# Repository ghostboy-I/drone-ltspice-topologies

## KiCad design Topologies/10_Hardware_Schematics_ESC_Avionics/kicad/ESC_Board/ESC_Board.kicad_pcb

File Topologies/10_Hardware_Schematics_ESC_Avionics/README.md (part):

# 10 — Hardware Schematics: ESC Board and Avionics Power Board

**Topology type:** topology 09 turned into two real PCBs with real parts. Each board is one LTspice schematic you can run, plus a BOM and a net list you can redraw in KiCad.

| Board | Qty per aircraft | What it does |
|---|---|---|
| **ESC board** (`ESC_Board.asc`) | 3 (one per motor) | 24S DC link → 3 × LTC7063 gate drivers → 24 × IPB065N15N3 (4 in parallel per switch) → U15XL. It has its own LTC7801 12 V aux supply, LT1763 5 V / 3.3 V, two ACS772 ±250 A current sensors and an STM32G431 running FOC. |
| **Avionics power board** (`Avionics_Board.asc`) | 1 | Three 24S packs → fuses + diode-OR → TVS + LTC4366 surge stopper (115 V) → LTC7801 12 V / 5 A (transmitter) → LT8641 5 V / 3 A (flight controller + receiver) → LT3045 3.3 V / 0.3 A (sensors). |

**Builds on:** [09](../09_24S_FOC_Drive_Low-Voltage_Rails/README.md) (the design these boards implement), [03](../03_Three-Phase_FOC_PMSM/README.md) (FOC), [06](../06_BEC_Synchronous_Buck_5V/README.md) (buck design), [08](../08_Redundant_Avionics_Power/README.md) (avionics fed from all three packs).
**Design document (with all the math):** `10_Hardware_Schematics_ESC_Avionics_Design.pdf`

## Files
| File | What it is |
|---|---|
| `board.py` | Builder: one parts table → `.asc` + BOM + net list (they can't drift apart) |
| `hand_calc.py` | All predictions (`python3 hand_calc.py`, `python3 hand_calc.py esc`) |
| `avionics.py`, `esc.py` | The two boards. `python3 avionics.py loop` also writes the loop-gain test |
| `*_BOM.csv` | Reference, quantity, description, value, part number / specification, **KiCad footprint**, rating |
| `*_Netlist.csv` | Every net with every `REF.pin` on it, the wiring list for KiCad (simulation-only parts removed) |
| `plot_results.py`, `make_design_doc.py` | Plots and the design PDF |
| `kicad_footprints.py`, `kicad_export.py`, `kicad_check.py` | KiCad: footprint library, both projects with PCBs, and the checks (see below) |
| `kicad_draw.py`, `kicad_avionics.py`, `kicad_esc.py`, `sexpr.py` | Both boards as drawn, hierarchical KiCad schematics (avionics five sheets, ESC eight), checked against the parts tables |
| `pcb_avionics.py`, `pcb_esc.py`, `kicad_route.py` | The two PCB layouts for JLCPCB: placement, pours, a grid router, DRC, Gerbers / BOM / CPL (see below) |

## Running the simulations
Open the `.asc` in LTspice and press Run, or in batch:
```bash
wine "$HOME/.wine/drive_c/Program Files/ADI/LTspice/LTspice.exe" -b ESC_Board.asc
```
| Run | Shows | Time |
|---|---|---|
| `Avionics_Board.asc` (8 ms) | Cold start and sequencing, transmitter switch-on, controller load step, pack 1 pulled | ~10 min |
| `Avionics_LoopTest.asc` | 12 V loop gain at 3 / 6 / 12 / 24 kHz by injection, on the switching circuit | ~5 min |
| `Avionics_SurgeTest.asc` (300 ms) | LTC4366 start-up, then pack 1 at 200 V behind 4 Ω for 20 ms: VIN_PROT must stay at 115 V | ~2 s |
| `ESC_Board.asc` (13 ms) | Cold start of the ESC electronics with the rotor at hover, flying start, throttle punch | ~7 min |

Parts named `V_…`, `B_…`, `L_HARN`, `R_CS…`, `R_BW…`, `C_BW…`, `La/Lb/Lc`, `C_J`, `C_TH`, `R_LK…`, `R_VBF`, `C_VBF`, `C_VTX`, `R_SSRUN`, `R_LOAD_SS` are simulation stimulus or models: the packs, the loads, the motor, and the STM32's FOC firmware as a behavioural block. Everything else is a board part with its real reference designator.

## Fixes from the parts-alternatives study
[Alternatives_Study](../Alternatives_Study/README.md) checked each section against datasheet ratings. Three problems are fixed here:
| Problem | Fix | Check |
|---|---|---|
| DC-link ripple 61.7 A rms at hover over 16 caps = 3.86 A each, above the 3.5 A rating | C65–C72: 8 more 150 µF 125 V hybrid polymer, 24 in all → 2.57 A each (3.48 A at punch, seconds only) | `python3 hand_calc.py changes`; ESC run `Icap_bulk`: 68.8 A → 2.87 A each at the run's iq of 160 A (hand 2.80) |
| Punch needs iq = 210 A; ACS770LCB-200B is specified to ±200 A | U7, U8 → ACS772ECB-250B: ±250 A, 8 mV/A, 200 kHz, same CB package and pinout. ADC still fits ±306 A, 151 mA/LSB | ESC run (firmware block uses 8 mV/A) |
| SMBJ110A clamps to 177 V at 3.4 A; the LTC7801 is rated to 150 V | U4 LTC4366-2 surge stopper + Q4 FDB33N25 (250 V): VIN_PROT held at VREG = 1.23 V (1 + R24/R23) = 115.3 V, 51 ms timer, 9 s cool-down | `Avionics_SurgeTest.asc`: 179 V in → 115.5 V out (hand 115.3 V) |

The LTC4366 takes ~0.1 s to turn Q4 on, so the 8 ms board run models Q4 already on (sim-only `R_SSRUN`, 94 mΩ), and its packs
ramp up from 0 V in 0.2 ms (the LTC4366 model has no DC operating point with the packs already at 88.8 V).

## Whole power system
The whole system, with both boards drawn part by part and wired to three packs and three motors, is now topology
[11](../11_Whole_System_Schematic/README.md) (`Power_System.asc`, the drawn board sheets and the KiCad entry guide).
The block diagram of everything, with part numbers, is in [System_Flowchart](../System_Flowchart/README.md).

## KiCad projects (both boards): schematic, footprints and PCB
```bash
python3 kicad_export.py all     # footprint library + both projects + overview plots
python3 kicad_check.py          # ERC, net list vs parts table, footprints, schematic-PCB parity (KiCad itself)
```
| Folder | What it is |
|---|---|
| `kicad/Drone_Power.pretty/` | **Every footprint both boards use (39).** 35 are KiCad 9 stock footprints, copied in under their KiCad names (`kicad_footprints.py`). 4 are not in KiCad's library and are generated from the manufacturers' drawings (table below) |
| `kicad/ESC_Board/` | The ESC board (197 parts): drawn schematic on eight sheets, and the **laid-out, routed PCB** (section below) |
| `kicad/Avionics_Board/` | The avionics board (77 parts): drawn schematic on five sheets, and the **laid-out, routed PCB** (next section) |
| `kicad/*_footprints.png` | KiCad's plot of each imported PCB: footprints parked by schematic block, ready for placement |

The PCBs are what **Tools → Update PCB from Schematic** would give: each footprint is linked to its symbol (same UUID path),
the nets come from KiCad's own net list of the schematic, and attributes (DNP, BOM) follow the symbols. The boards are laid
out by `pcb_avionics.py` and `pcb_esc.py`.

| Generated footprint | Part | Source |
|---|---|---|
| `Linear_UDC-18-2EP_3x4mm_P0.5mm` | LT8641 (avionics U2) | LT8641 datasheet Rev B: UDC 20(18)-lead QFN 3 × 4 mm, DWG 05-08-1956 Rev C. 0.25 × 0.70 mm lands at 0.5 mm, pins 5 and 12 removed, two exposed SW pads (21: 0.22 × 0.40 mm, 22: 0.22 × 0.356 mm) |
| `Linear_HTSSOP-24-1EP_4.4x7.8mm_P0.65mm_EP2.74x3.25mm` | LTC7801 (U1, both boards) | LTC DWG 05-08-1771 Rev B, FE24 exposed pad variation AA: 0.45 × 1.05 mm lands, exposed pad 2.74 × 3.25 mm = GND, 2 × 2 paste windows |
| `AMASS_AS150_Pigtail_2x8AWG_P15mm` | J1, ESC battery input | The AS150's two 8 AWG pigtail leads: 5.1 mm drill, 8.4 mm pads, 15 mm pitch (6.6 mm copper gap on the 100 V bus). Pad 1 = +, pad 2 = − |
| `SolderWire-8AWG_1x01_D4.2mm_OD7mm` | J2–J4, motor phase leads | 8 AWG silicone lead (4.2 mm conductor): KiCad's wire-pad rule, drill = conductor + 0.9 mm |

**Checked** (`kicad_check.py`): ERC 0 errors / 0 warnings on both boards; KiCad's net list equals the parts table on all
92 + 40 nets; every symbol pin has a pad of the same number; schematic-PCB parity 0 issues; polarised capacitors have pad 1
(+) off ground. Pads without a net are only unused MCU pins, the LTC7063 NC pins, TC2030 pad 6 (SWO) and connector
mounting tabs. Re-running the export gives identical files (UUIDs are derived from the board name).

**Corrected while importing the footprints**
- The LTC7801 had been given an HTSSOP-24 footprint whose 3.2 × 5 mm exposed pad comes from an ST drawing; ADI's FE24 pad is
  2.74 × 3.25 mm, so that land would have printed about 1.8× too much solder paste under the chip.
- The LT8641 is in ADI's UDC QFN (LT8641EUDC#PBF), not an LQFN: the BOM part number and package are fixed.
- J7 (Tag-Connect TC2030) had SWCLK and NRST swapped against the TC2030-CTX cable (pads 1 VCC, 2 SWDIO, 3 nRESET, 4 SWCLK,
  5 GND): now NRST is pad 3 and SWCLK pad 4.
- The motor phase pads were KiCad's 2.5 mm² wire pad, far too small for the 6–8 AWG phase leads; now 8 AWG pads.
- SMBJ110A is unidirectional, so it uses `Device:D_Zener` (K = 1, A = 2) instead of the bidirectional `D_TVS`; fuses use `Device:Fuse`.

## Avionics PCB layout (JLCPCB, 4 layers)
```bash
python3 pcb_avionics.py         # schematic -> placed, poured, routed, filled board + DRC + layout_routed.png (a few minutes)
python3 pcb_avionics.py place   # placement only, with layout_place.png
python3 pcb_avionics.py fab     # kicad/Avionics_Board/jlcpcb/: Gerber zip, BOM and CPL for JLC
```
The layout is a script, so a schematic change is one re-run. **Board:** 100 × 62 mm, 4 layers, 1.6 mm, 2 oz outer / 1 oz
inner (JLC04161H-7628 stackup), four M3 holes. In1 and In2 are solid ground planes; F.Cu carries the power pours; B.Cu has a
ground pour and the signal crossings. Power flows left to right: inputs → surge stopper → 12 V → 5 V → 3.3 V.

**Clearance rules** (`Avionics_Board.kicad_dru`, IPC-2221B table 6-1, B2 = external, uncoated). The spacing between two
conductors depends on the voltage *between* them, so nets are grouped by their peak voltage from the surge simulation:

| Group (net class) | Nets | Peak | Outer-layer clearance |
|---|---|---|---|
| HVIN | PACK1–3+, PACK1–3_F, VIN_AV | 200 V (pack surge) | 1.25 mm to LV and HVSW, 0.6 mm to HVF |
| HVF | VIN_PROT and the floating LTC4366 nets | ≤ 122 V | 0.6 mm |
| HVSW | SW12, BST12, TG12 | 0–126 V | 0.6 mm |
| LV (PWR, DRV, signal) | +12V, +5V, +3V3, GND, gate drive, control | ≤ 13 V | 0.2 mm |

Inner layers use 0.5 mm (B1 asks only 0.2 mm). Inside a group the spacing is 0.2 mm. The LTC7801's own pinout puts VIN 0.65 mm
from low-voltage pins, so its pin field (`U1_PINS` rule area, F.Cu) allows 0.2 mm. **Conformal-coat the board** (IPC B4).

**How it is checked**
- KiCad's DRC (`kicad-cli pcb drc` with schematic parity): `Avionics_Board_drc.json`, summary in `layout_stats.json`.
- `pinfield_audit()`: the U1 exemption must not reach copper outside the pin field. Every exempt item is cut back to the
  copper outside the area and the gaps that are left must meet the full rule.
- Before trusting a DRC of 0, make sure it loaded the rules. pcbnew's `LoadBoard` skips the `.kicad_dru`, so the zone filler
  needs the rules loaded first (`WriteDRCReport`). A reload in the same process also reuses a cached project, net classes and all.
  The script handles both (`fill()`, `load()`), and `load()` asserts that the HV classes are present.

**Results** (from `layout_stats.json`): 77 parts + 4 M3 holes; 512 tracks (F.Cu 498 mm, B.Cu 225 mm) and 114 vias; **0 unrouted, KiCad DRC 0 errors / 0 warnings with the HV rules loaded, schematic parity 0, pin-field audit 0.** Measured independently (KiCad's shape collision test), the ground pours sit ≥ 1.25 mm from HVIN copper and ≥ 0.6 mm from HVF / HVSW on the outer layers, and ≥ 0.5 mm on the inner planes. C10 and C23 have their references on F.Fab only (no silkscreen room).

`board_3d_top.png` is `kicad-cli pcb render --side top`. U1, U2 and the input connectors have no 3D model, so you see their pads.

**Ordering at JLCPCB** (`kicad/Avionics_Board/jlcpcb/`): upload `Avionics_Board_gerbers.zip`, choose 4 layers, 1.6 mm,
outer copper 2 oz, inner 1 oz, impedance control off (stackup JLC04161H-7628). For assembly, add `Avionics_Board_BOM_JLC.csv`
and `Avionics_Board_CPL_JLC.csv`. The LCSC column is empty, so pick each part in JLC's matcher, and **check every rotation
in JLC's 3D preview**: zero orientations differ between KiCad and JLC for SOT-23s, diodes and polarised parts.

Open items before ordering:
- F1–F3 are rated 125 V DC, but the surge test drives a pack input to 200 V. The fuse only has to survive it, not break
  it (the TVS and LTC4366 clamp downstream), but a 250 V DC-rated fuse in the same footprint removes the question.
- C26 is the 250 V 1206 part (it sits on the 100–121 V node).

## ESC PCB layout (JLCPCB, 4 layers + bus bars)
```bash
python3 pcb_esc.py              # schematic -> placed, poured, routed, filled board + DRC + renders + stats (~6 min)
python3 pcb_esc.py place        # placement only, with layout_place.png
python3 pcb_esc.py copper       # power copper and hand vias only, filled, with layout_copper.png and DRC
python3 pcb_esc.py check        # independent clearance measurement of the saved board, into layout_stats.json
python3 pcb_esc.py fab          # kicad/ESC_Board/jlcpcb/: Gerber zip, BOM and CPL for JLC
```
**Board:** 175 × 130 mm, 4 layers, 1.6 mm, 2 oz outer / 1 oz inner (JLC04161H-7628), four M3 holes. The floorplan follows
the current. At the top is the DC link: 24 polymer capacitors in three rows of eight, with the battery pigtail J1 to their
right. Below them sit the three legs side by side, each a column of four high-side D2PAKs, a phase lane, four low-side
D2PAKs and a ground lane. The next leg's DC-link ceramics sit across each ground lane. Along the bottom is the low-current
band (drivers, current sensors, motor-lead pads, MCU, LDOs, connectors), and the aux 12 V buck is in the top-right corner.
Battery current flows top to bottom and motor current leaves at the bottom, so no high current crosses the MCU, and one
solid ground plane (In1) serves power and signal ground.

**Power copper.** VBUS, the phases and ground are pours on all four layers, sized by counting squares (design doc sec. 9).
Mask-free strips take a soldered copper bar (4 × 2 mm, or flattened 8 AWG): the three phase lanes, the VBUS strip along
the tops of the legs and the bridge from J1. Every FET tab has 30 thermal vias. The B.Cu under each FET column is opened
for the heat sink, which needs an insulating pad, because that copper is at VBUS or phase potential.

**Clearance rules** (`ESC_Board.kicad_dru`). These are the avionics board's groups, extended to 24S (100.8 V):

| Group (net class) | Nets | Voltage | Outer clearance |
|---|---|---|---|
| HVBUS | VBUS | 0–100.8 V | 0.6 mm to every other class |
| SW_A / SW_B / SW_C | PH_x, BST_x, TG_x, HS gates, MOT_x | −1 to 113 V | 0.6 mm (0.2 mm inside one phase) |
| SW_AUX | aux SW, BST, TG | 0–113 V | 0.6 mm |
| HVDIV1 / HVDIV2 | bus divider taps | 67 V / 34 V | 0.6 mm |
| LV (PWR, DRV, signal) | GND, +12V, +5V, +3V3, LS gates, control | ≤ 13 V | 0.2 mm |

Each phase is its own group: two phases can be the full bus apart, while a phase, its bootstrap supply and its high-side
gates move together. Inner layers use 0.3 mm (B1 asks only 0.2 mm). The LTC7063s and the LTC7801 put 100 V pins 0.2–0.25 mm from
low-voltage ones, so their pin fields are exempt rule areas (0.2 mm), checked by `pinfield_audit()`. **Conformal-coat the board.**

**Routing.** This uses the same A* router (`kicad_route.py`), with the hard spots planned by hand:
- **The LTC7801's left pin row escapes through a two-column via fan-out** (alternate pins 1.22 / 2.27 mm out). VBUS sits
  between NDRV and EXTVCC there, so no single-layer order works (What went wrong, 13).
- **FAULT_N drops to B.Cu through a via under each driver's pin 3.** It and DRV_EN are buses on neighbouring pins of all
  three drivers, so whichever routes first walls in the other.
- **R5's +3V3 routes before the encoder bus**, which would otherwise wall it in.
- **`tidy()` necks a track down to the pad's narrow side less 0.05 mm where it ends in a pad.** The router snaps the
  last point onto the exact pad centre, up to 25 µm off the grid it checked. `tidy()` also removes vias that two
  fan-outs put on the same spot.
- **Fan-out vias keep the full grid error** (cell × √2). KiCad's DRC caught one placed with only 0.75 cell, 0.196 mm from
  an LQFP pin.

**How it is checked**
- KiCad's DRC with schematic parity, with the HV rules loaded: `ESC_Board_drc.json`.
- `pinfield_audit()`: the exemptions must not reach copper outside the pin fields.
- `measure_gaps()` is an independent measurement that doesn't use KiCad's DRC engine. Per layer, all copper of each group
  (pads, tracks, vias, zone fills) becomes one polygon set. One set is grown by d (Clipper) and intersected with the
  other, bisecting d to 1 µm.

**Results** (`layout_stats.json`): 197 parts + 4 M3 holes; 1061 tracks (F.Cu 1598 mm, B.Cu
1161 mm) and 2147 vias (1974 placed by hand: 720 in FET tabs, 468 at the FET sources,
429 in the ground lanes, 288 in the capacitor bank). **0 unrouted, KiCad DRC 0 errors / 0 warnings, schematic parity 0,
pin-field audit 0.** Measured independently, every HV group keeps at least 0.600 mm from the other groups on F.Cu and B.Cu
and 0.300 mm on In1/In2. The closest pairs sit exactly at the rule, where the zone filler puts a pour.
6 references (Q8, Q25, Q17, R12, R15, R14) are on F.Fab only, because there was no room on the silkscreen.

**Ordering at JLCPCB** (`kicad/ESC_Board/jlcpcb/`): upload `ESC_Board_gerbers.zip` and choose:
- 4 layers, 1.6 mm, outer copper 2 oz, inner 1 oz.
- **Via covering "epoxy filled & capped"**: the thermal vias sit in the D2PAK tab pads, so open vias would wick the solder away.

For assembly, add `ESC_Board_BOM_JLC.csv` and `ESC_Board_CPL_JLC.csv`. The LCSC column is empty, so pick each part in JLC's
matcher, and check every rotation in JLC's 3D preview (D2PAKs, diodes, polarised capacitors, SOT-223).

Fit by hand after assembly:
1. Solder the copper bars on the mask-free strips.
2. Fit J1 (AS150 pigtails) and the 8 AWG motor leads.
3. Fit the heat sink over a ≥ 0.5 mm, ≥ 3 W/m·K, 150 V-rated insulating pad.
4. Conformal-coat the board.

R6 (the NTC) sits at the bottom of leg B's ground lane, on the board copper next to the FETs, not on the sink.

## Porting to KiCad by hand
1. **One schematic per board**, with one hierarchical sheet per numbered block (the framed areas in the `.asc`): e.g. ESC = 1 power input, 2 aux supply, 3 logic supplies, 4–6 legs A/B/C, 7 current sense, 8 MCU and connectors. Use global labels for the nets that cross sheets (`VBUS`, `+12V`, `+5V`, `+3V3`, `PWM_A`…).
2. **Symbols.** KiCad's stock library has the STM32G431CBTx, the ACS770/ACS772 CB-package symbol, the LT3045 and the AS5047. The **LTC7801, LTC7063, LT8641, LT1763 and LTC4366 are not in KiCad's library**: use the generated ones in `kicad/<Board>/<Board>_custom.kicad_sym`. Pin names in the net list are LTspice's names (`SENSE+`, `BGRTN`, `_FLT` = FLT-bar, `_SHDN` = SHDN-bar); match them to the datasheet pin names, not to pin numbers.
3. **Wire from `*_Netlist.csv`**: each row is one net and every pin on it. Parts listed with a quantity (e.g. `Q4 Q5 Q6 Q7`) are parallel copies with identical connections.
4. **Footprints** are all in `kicad/Drone_Power.pretty` (add it to your footprint library table). The BOM gives each one by its KiCad library name; the four `Drone_Power:` ones are generated from the manufacturers' drawings.
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
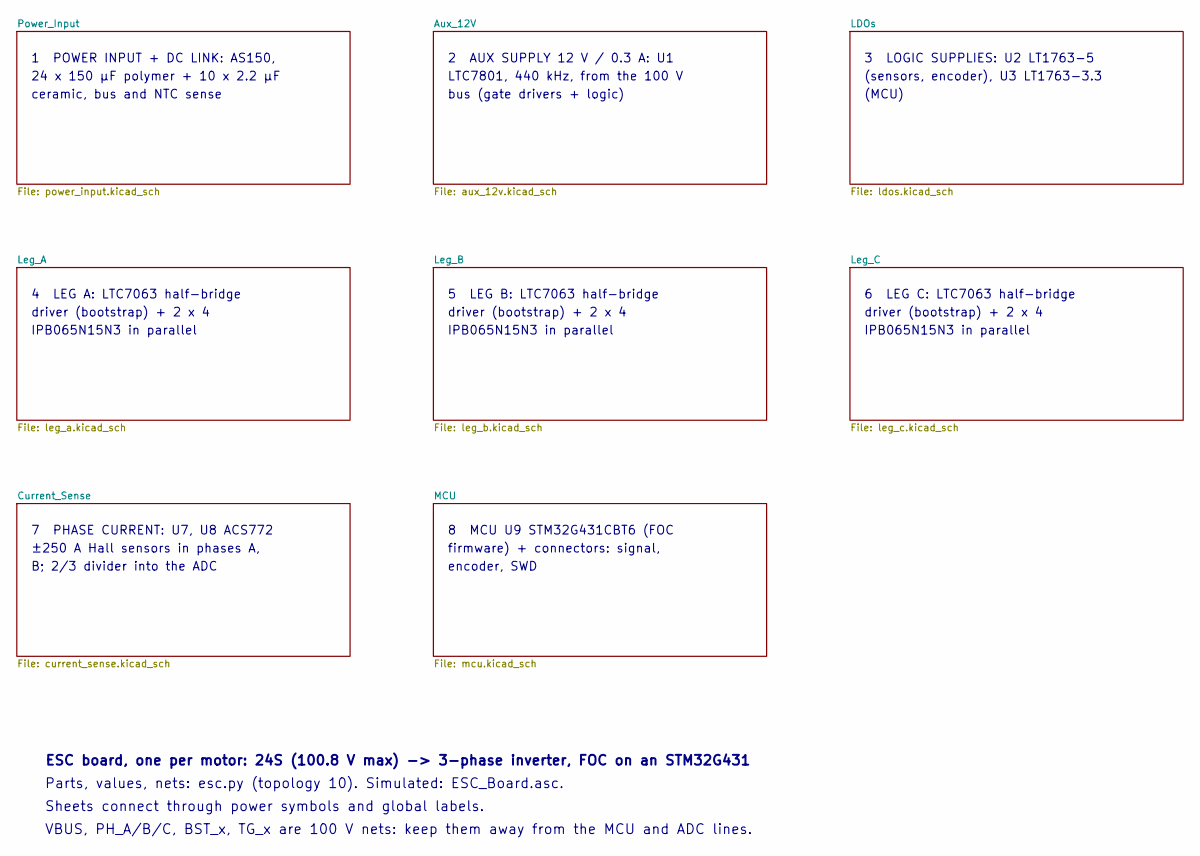
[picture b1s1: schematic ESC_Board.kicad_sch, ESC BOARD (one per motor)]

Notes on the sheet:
1 POWER INPUT + DC LINK: AS150,
24 x 150 µF polymer + 10 x 2.2 µF
ceramic, bus and NTC sense
2 AUX SUPPLY 12 V / 0.3 A: U1
LTC7801, 440 kHz, from the 100 V
bus (gate drivers + logic)
3 LOGIC SUPPLIES: U2 LT1763-5
(sensors, encoder), U3 LT1763-3.3
(MCU)
4 LEG A: LTC7063 half-bridge
driver (bootstrap) + 2 x 4
IPB065N15N3 in parallel
5 LEG B: LTC7063 half-bridge
6 LEG C: LTC7063 half-bridge
7 PHASE CURRENT: U7, U8 ACS772
±250 A Hall sensors in phases A,
B; 2/3 divider into the ADC
8 MCU U9 STM32G431CBT6 (FOC
firmware) + connectors: signal,
encoder, SWD
ESC board, one per motor: 24S (100.8 V max) -> 3-phase inverter, FOC on an STM32G431
Parts, values, nets: esc.py (topology 10). Simulated: ESC_Board.asc.
Sheets connect through power symbols and global labels.
VBUS, PH_A/B/C, BST_x, TG_x are 100 V nets: keep them away from the MCU and ADC lines.

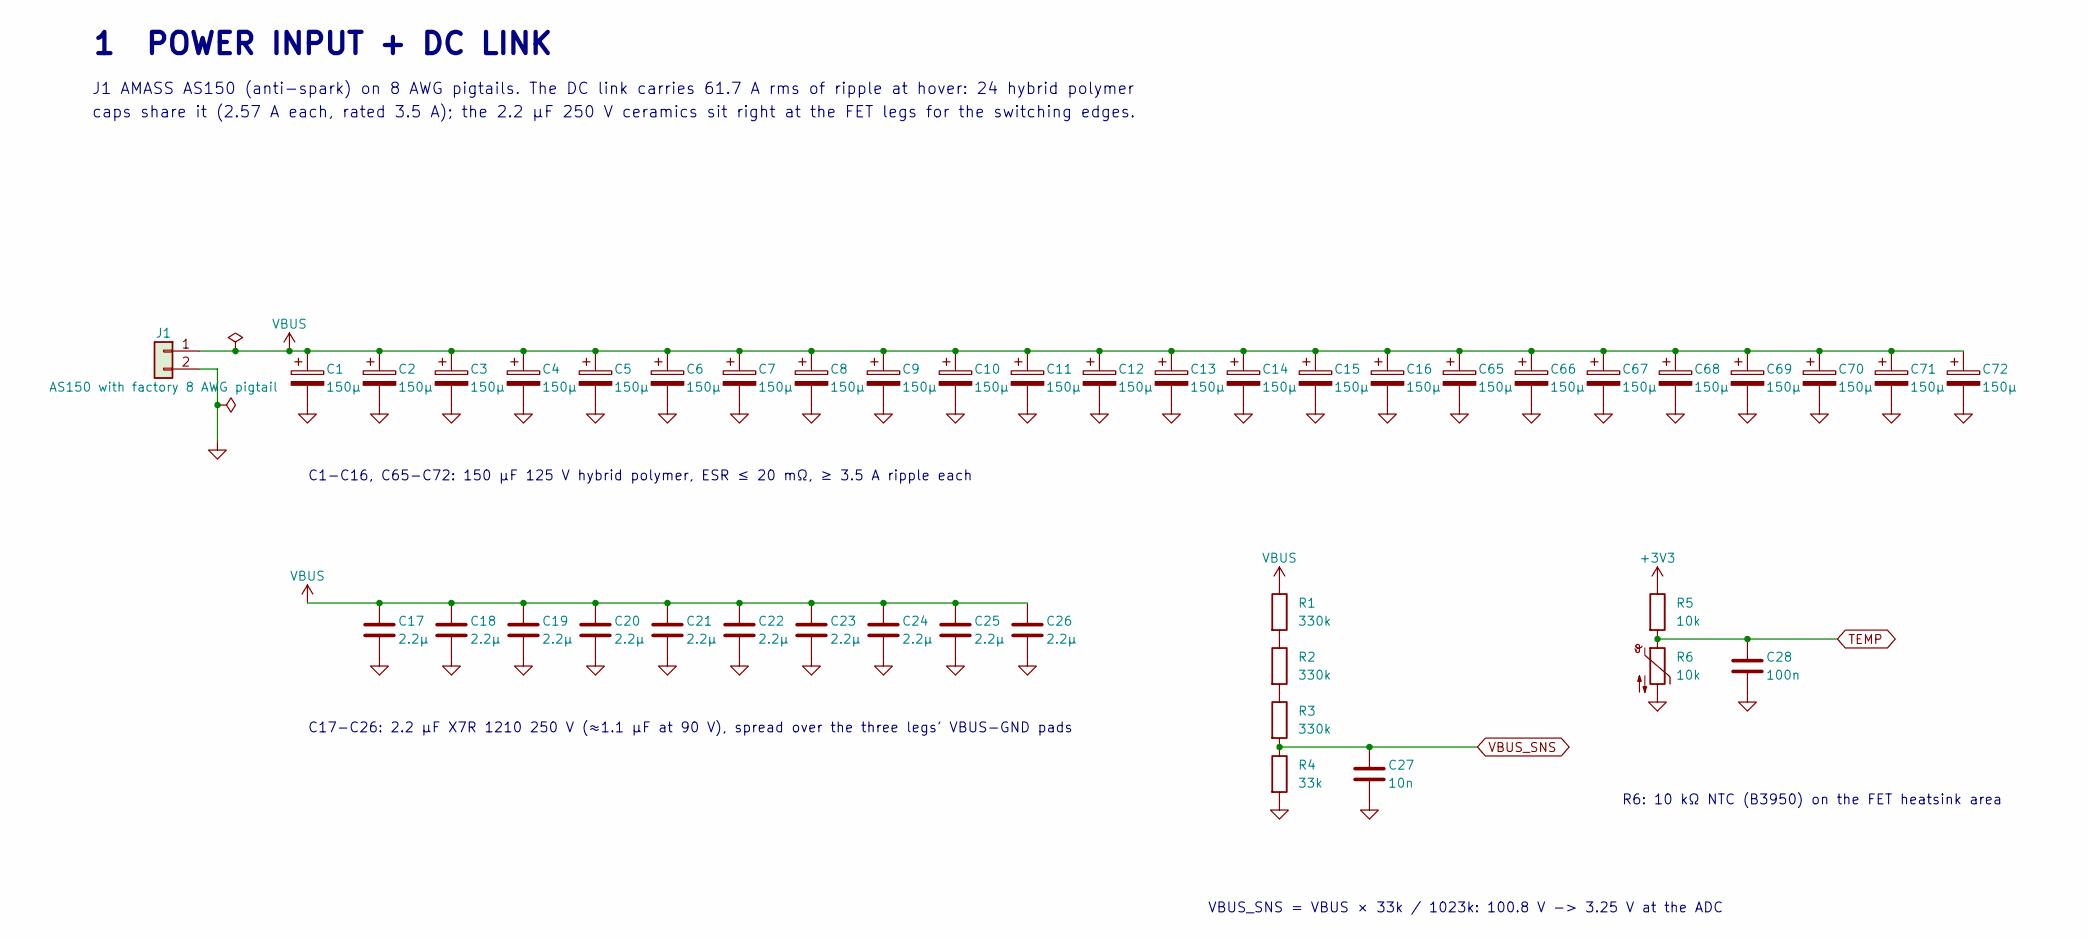
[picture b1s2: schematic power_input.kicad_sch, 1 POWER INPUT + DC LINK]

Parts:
C1, C2, C3, C4, C5, C6, C7, C8, C9, C10, C11, C12, C13, C14, C15, C16, C65, C66, C67, C68, C69, C70, C71, C72: 150µ; CP_Elec_10x12.5; Rating 125 V; MPN/Spec 150 µF 125 V hybrid polymer, ≥3.5 A rip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
C17, C18, C19, C20, C21, C22, C23, C24, C25, C26: 2.2µ; C_1210_3225Metric; Rating 250 V; MPN/Spec 2.2 µF X7R 1210 (≈1.1 µF at 90 V)
C27: 10n; C_0603_1608Metric; MPN/Spec X7R
C28: 100n; C_0603_1608Metric; MPN/Spec X7R
J1: AS150 with factory 8 AWG pigtail; AMASS_AS150_Pigtail_2x8AWG_P15mm; Rating 150 A, 24S; MPN/Spec AMASS AS150 with factory 8 AWG pigtail 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
R1, R2, R3: 330k; R_1206_3216Metric; Rating 200 V; MPN/Spec 1 %, thick film
R4: 33k; R_0603_1608Metric; MPN/Spec 1 %, thick film
R5: 10k; R_0603_1608Metric; MPN/Spec 1 %, thick film
R6: 10k; R_0603_1608Metric; MPN/Spec NTC 10 kΩ B3950

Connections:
+3V3: R5.1; also elsewhere on the board
GND: C1.2, C2.2, C3.2, C4.2, C5.2, C6.2, C7.2, C8.2, C9.2, C10.2, C11.2, C12.2, C13.2, C14.2, C15.2, C16.2, C17.2, C18.2, C19.2, C20.2, C21.2, C22.2, C23.2, C24.2, C25.2, C26.2, C27.2, C28.2, C65.2, C66.2, C67.2, C68.2, C69.2, C70.2, C71.2, C72.2, J1.2, R4.2, R6.2; also elsewhere on the board
unnamed: R1.2, R2.1
unnamed: R2.2, R3.1
TEMP: C28.1, R5.2, R6.1; also elsewhere on the board
VBUS: C1.1, C2.1, C3.1, C4.1, C5.1, C6.1, C7.1, C8.1, C9.1, C10.1, C11.1, C12.1, C13.1, C14.1, C15.1, C16.1, C17.1, C18.1, C19.1, C20.1, C21.1, C22.1, C23.1, C24.1, C25.1, C26.1, C65.1, C66.1, C67.1, C68.1, C69.1, C70.1, C71.1, C72.1, J1.1, R1.1; also elsewhere on the board
VBUS_SNS: C27.1, R3.2, R4.1; also elsewhere on the board

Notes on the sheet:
1 POWER INPUT + DC LINK
J1 AMASS AS150 (anti-spark) on 8 AWG pigtails. The DC link carries 61.7 A rms of ripple at hover: 24 hybrid polymer
caps share it (2.57 A each, rated 3.5 A); the 2.2 µF 250 V ceramics sit right at the FET legs for the switching edges.
C1-C16, C65-C72: 150 µF 125 V hybrid polymer, ESR ≤ 20 mΩ, ≥ 3.5 A ripple each
C17-C26: 2.2 µF X7R 1210 250 V (≈1.1 µF at 90 V), spread over the three legs' VBUS-GND pads
VBUS_SNS = VBUS × 33k / 1023k: 100.8 V -> 3.25 V at the ADC
R6: 10 kΩ NTC (B3950) on the FET heatsink area

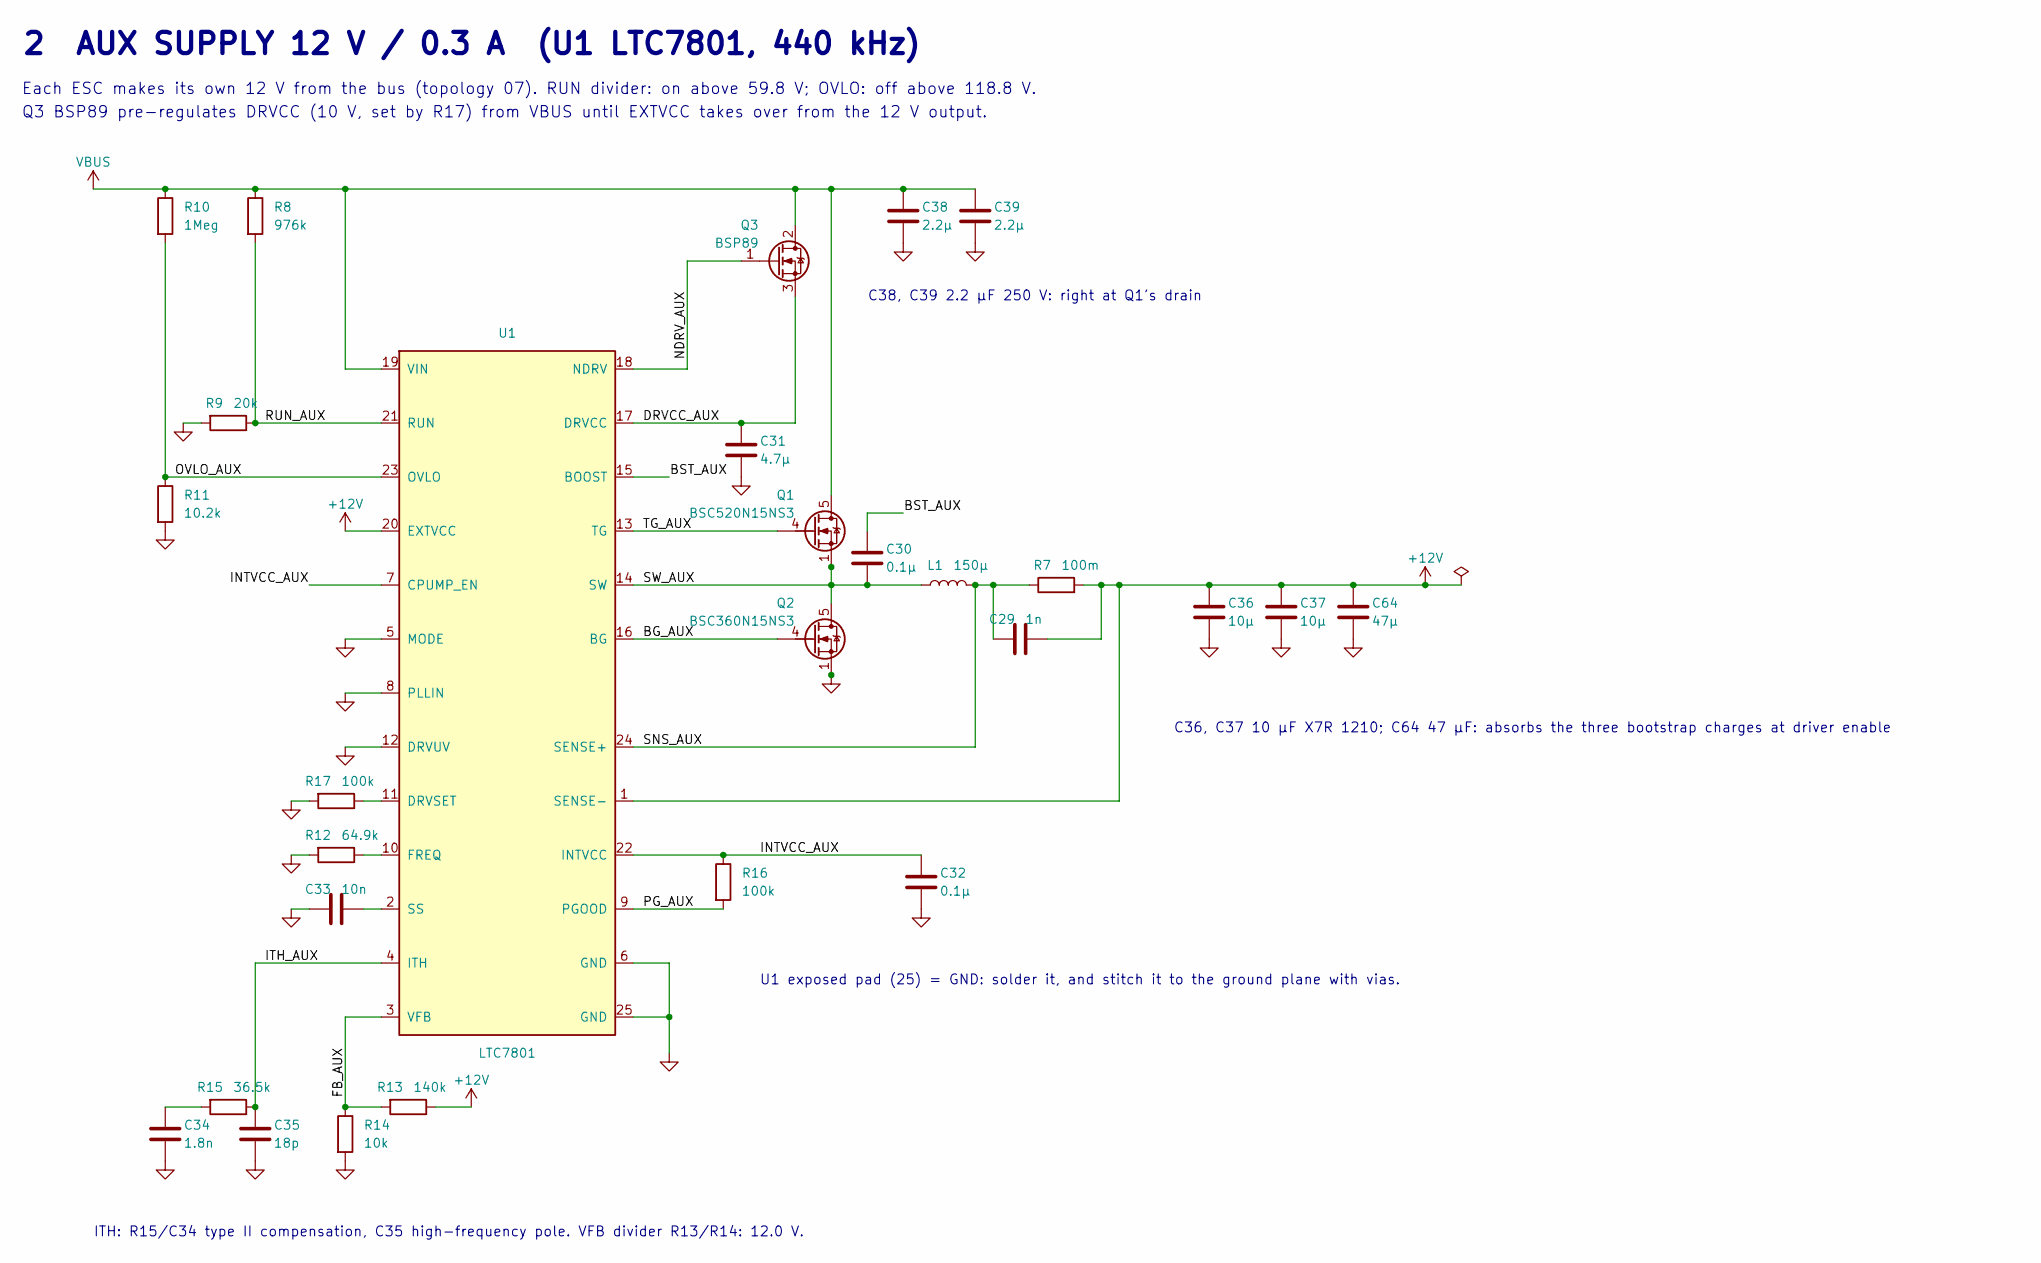
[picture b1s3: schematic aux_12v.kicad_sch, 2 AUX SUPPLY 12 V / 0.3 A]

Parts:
C29: 1n; C_0603_1608Metric; MPN/Spec X7R
C30: 0.1µ; C_0603_1608Metric; Rating 25 V; MPN/Spec X7R
C31: 4.7µ; C_0805_2012Metric; Rating 25 V; MPN/Spec X7R
C32: 0.1µ; C_0603_1608Metric; MPN/Spec X7R
C33: 10n; C_0603_1608Metric; MPN/Spec X7R
C34: 1.8n; C_0603_1608Metric; MPN/Spec X7R
C35: 18p; C_0603_1608Metric; MPN/Spec X7R
C36, C37: 10µ; C_1210_3225Metric; Rating 25 V; MPN/Spec 10 µF X7R 1210 (5 µF at 12 V)
C38, C39: 2.2µ; C_1210_3225Metric; Rating 250 V; MPN/Spec 2.2 µF X7R 1210 (≈1.1 µF at 90 V)
C64: 47µ; C_1210_3225Metric; Rating 25 V; MPN/Spec 47 µF X7R 1210 (≈22 µF at 12 V)
L1: 150µ; L_Bourns_SRR1260; Rating Isat 1 A; MPN/Spec shielded, Isat ≥ 1 A, DCR ≤ 0.4 Ω
Q1: BSC520N15NS3; TDSON-8-1; Rating 150 V 21 A; MPN/Spec Infineon BSC520N15NS3
Q2: BSC360N15NS3; TDSON-8-1; Rating 150 V 30 A; MPN/Spec Infineon BSC360N15NS3
Q3: BSP89; SOT-223-3_TabPin2; Rating 240 V; MPN/Spec Infineon BSP89
R7: 100m; R_0805_2012Metric; Rating 0.25 W; MPN/Spec current sense 1 %
R8: 976k; R_1206_3216Metric; Rating 200 V; MPN/Spec 1 %, thick film
R9: 20k; R_0603_1608Metric; MPN/Spec 1 %, thick film
R10: 1Meg; R_1206_3216Metric; Rating 200 V; MPN/Spec 1 %, thick film
R11: 10.2k; R_0603_1608Metric; MPN/Spec 1 %, thick film
R12: 64.9k; R_0603_1608Metric; MPN/Spec 1 %, thick film
R13: 140k; R_0603_1608Metric; MPN/Spec 1 %, thick film
R14: 10k; R_0603_1608Metric; MPN/Spec 1 %, thick film
R15: 36.5k; R_0603_1608Metric; MPN/Spec 1 %, thick film
R16, R17: 100k; R_0603_1608Metric; MPN/Spec 1 %, thick film
U1: LTC7801; Linear_HTSSOP-24-1EP_4.4x7.8mm_P0.65mm_EP2.74x3.25mm; Rating 150 V; MPN/Spec LTC7801EFE (TSSOP-24 with exposed pad)

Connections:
+12V: C29.2, C36.1, C37.1, C64.1, R7.2, R13.1, U1.1 (SENSE-), U1.20 (EXTVCC); also elsewhere on the board
/Aux_12V/BG_AUX: Q2.4 (G), U1.16 (BG)
/Aux_12V/BST_AUX: C30.1, U1.15 (BOOST)
/Aux_12V/DRVCC_AUX: C31.1, Q3.3 (S), U1.17 (DRVCC)
/Aux_12V/FB_AUX: R13.2, R14.1, U1.3 (VFB)
/Aux_12V/INTVCC_AUX: C32.1, R16.1, U1.7 (CPUMP_EN), U1.22 (INTVCC)
/Aux_12V/ITH_AUX: C35.1, R15.1, U1.4 (ITH)
/Aux_12V/NDRV_AUX: Q3.1 (G), U1.18 (NDRV)
/Aux_12V/OVLO_AUX: R10.2, R11.1, U1.23 (OVLO)
/Aux_12V/PG_AUX: R16.2, U1.9 (PGOOD)
/Aux_12V/RUN_AUX: R8.2, R9.1, U1.21 (RUN)
/Aux_12V/SNS_AUX: C29.1, L1.2, R7.1, U1.24 (SENSE+)
/Aux_12V/SW_AUX: C30.2, L1.1, Q1.1 (S), Q1.2 (S), Q1.3 (S), Q2.5 (D), U1.14 (SW)
/Aux_12V/TG_AUX: Q1.4 (G), U1.13 (TG)
GND: C31.2, C32.2, C33.2, C34.2, C35.2, C36.2, C37.2, C38.2, C39.2, C64.2, Q2.1 (S), Q2.2 (S), Q2.3 (S), R9.2, R11.2, R12.2, R14.2, R17.2, U1.5 (MODE), U1.6 (GND), U1.8 (PLLIN), U1.12 (DRVUV), U1.25 (GND); also elsewhere on the board
unnamed: C34.1, R15.2
unnamed: R17.1, U1.11 (DRVSET)
unnamed: R12.1, U1.10 (FREQ)
unnamed: C33.1, U1.2 (SS)
VBUS: C38.1, C39.1, Q1.5 (D), Q3.2 (D), R8.1, R10.1, U1.19 (VIN); also elsewhere on the board

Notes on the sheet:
2 AUX SUPPLY 12 V / 0.3 A (U1 LTC7801, 440 kHz)
Each ESC makes its own 12 V from the bus (topology 07). RUN divider: on above 59.8 V; OVLO: off above 118.8 V.
Q3 BSP89 pre-regulates DRVCC (10 V, set by R17) from VBUS until EXTVCC takes over from the 12 V output.
ITH: R15/C34 type II compensation, C35 high-frequency pole. VFB divider R13/R14: 12.0 V.
C38, C39 2.2 µF 250 V: right at Q1's drain
C36, C37 10 µF X7R 1210; C64 47 µF: absorbs the three bootstrap charges at driver enable
U1 exposed pad (25) = GND: solder it, and stitch it to the ground plane with vias.

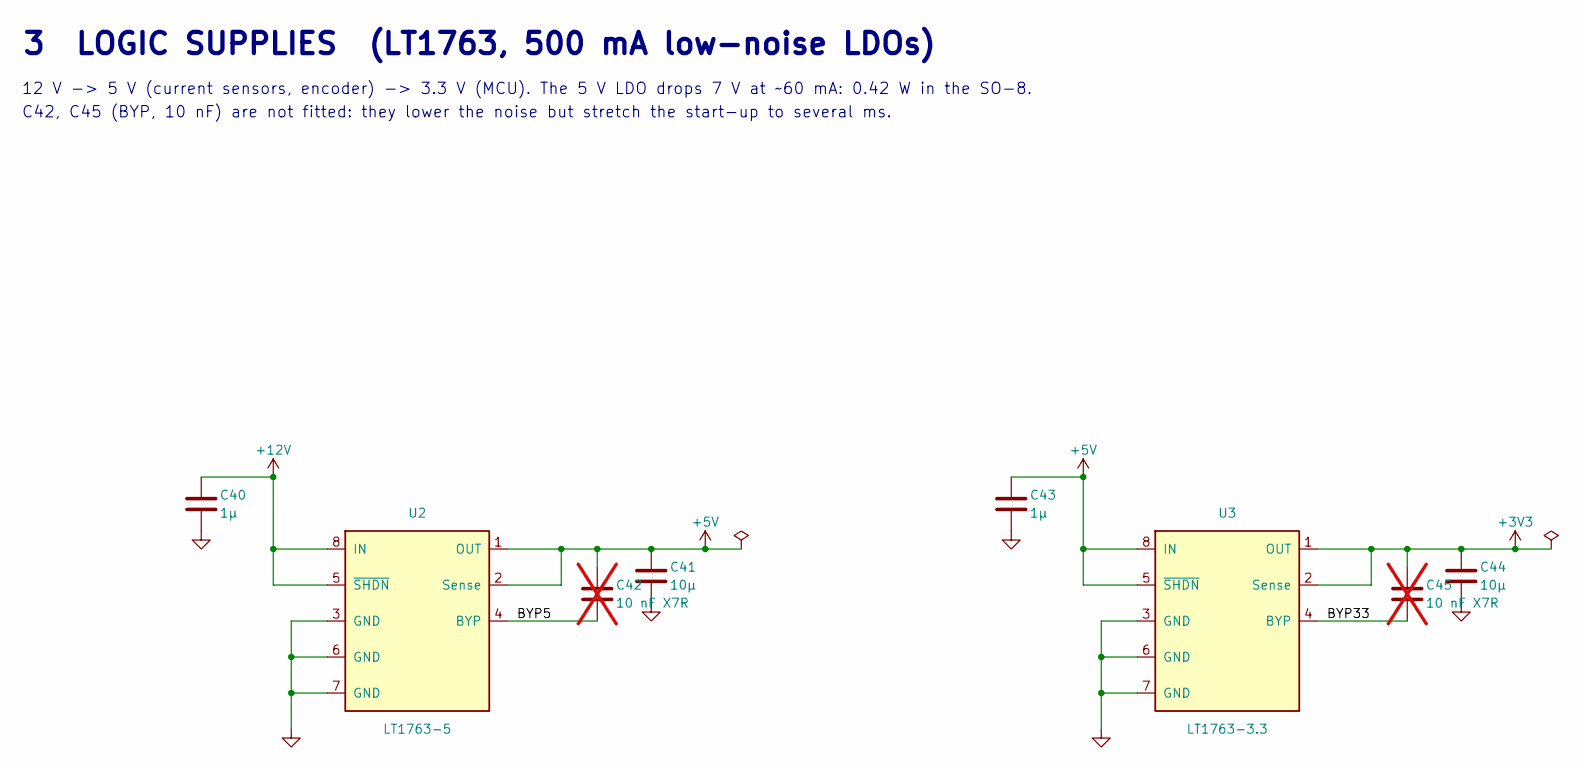
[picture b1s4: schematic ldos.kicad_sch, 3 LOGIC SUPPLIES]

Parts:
C40: 1µ; C_0805_2012Metric; Rating 25 V; MPN/Spec X7R
C41, C44: 10µ; C_0805_2012Metric; Rating 10 V; MPN/Spec X7R
C42, C45: 10 nF X7R; C_0603_1608Metric; MPN/Spec 10 nF X7R, DNP; not fitted
C43: 1µ; C_0805_2012Metric; Rating 10 V; MPN/Spec X7R
U2: LT1763-5; SOIC-8_3.9x4.9mm_P1.27mm; Rating 20 V; MPN/Spec LT1763CS8-5 (SO-8)
U3: LT1763-3.3; SOIC-8_3.9x4.9mm_P1.27mm; Rating 20 V; MPN/Spec LT1763CS8-3.3 (SO-8)

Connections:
+3V3: C44.1, C45.1, U3.1 (OUT), U3.2 (Sense); also elsewhere on the board
+5V: C41.1, C42.1, C43.1, U2.1 (OUT), U2.2 (Sense), U3.5 (~SHDN), U3.8 (IN); also elsewhere on the board
+12V: C40.1, U2.5 (~SHDN), U2.8 (IN); also elsewhere on the board
/LDOs/BYP5: C42.2, U2.4 (BYP)
/LDOs/BYP33: C45.2, U3.4 (BYP)
GND: C40.2, C41.2, C43.2, C44.2, U2.3 (GND), U2.6 (GND), U2.7 (GND), U3.3 (GND), U3.6 (GND), U3.7 (GND); also elsewhere on the board

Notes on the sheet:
3 LOGIC SUPPLIES (LT1763, 500 mA low-noise LDOs)
12 V -> 5 V (current sensors, encoder) -> 3.3 V (MCU). The 5 V LDO drops 7 V at ~60 mA: 0.42 W in the SO-8.
C42, C45 (BYP, 10 nF) are not fitted: they lower the noise but stretch the start-up to several ms.

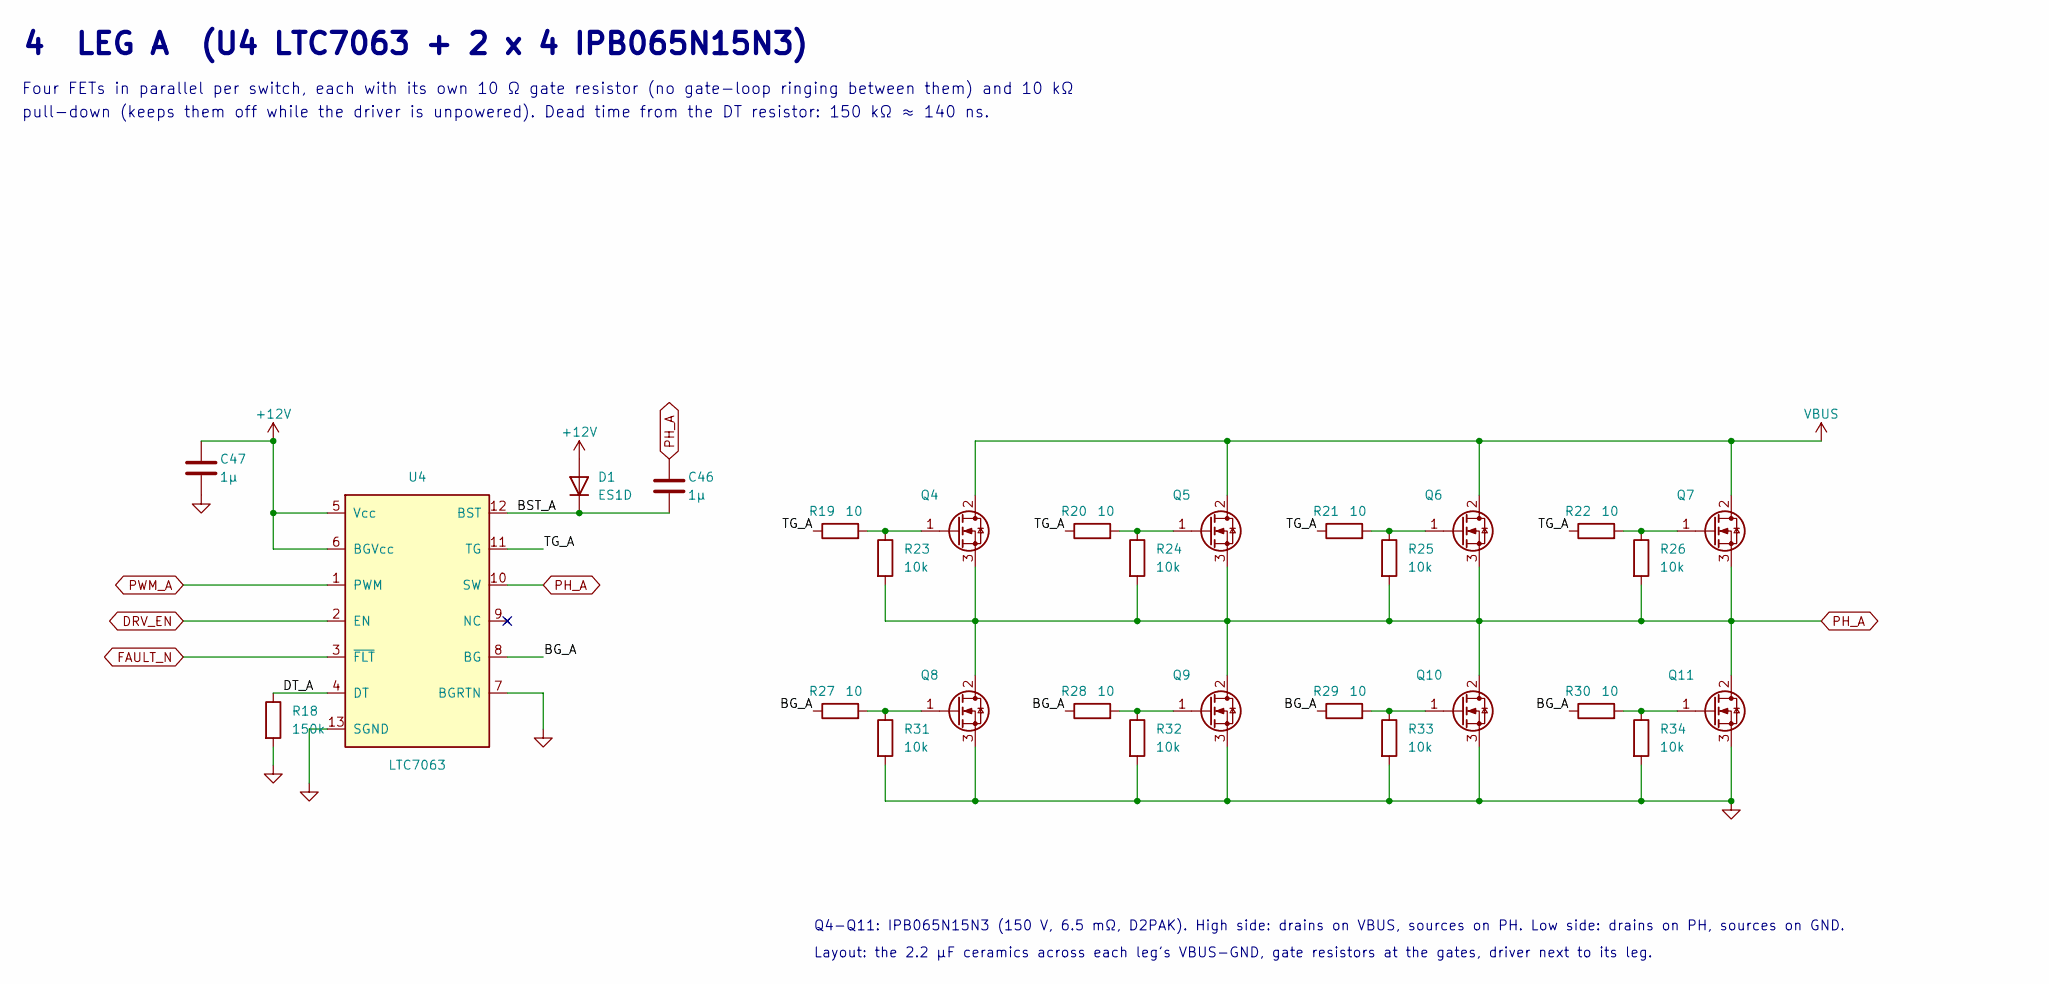
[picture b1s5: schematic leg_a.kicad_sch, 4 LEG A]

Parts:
C46, C47: 1µ; C_0805_2012Metric; Rating 25 V; MPN/Spec X7R
D1: ES1D; D_SMA; Rating 200 V 1 A; MPN/Spec ES1D
Q4, Q5, Q6, Q7, Q8, Q9, Q10, Q11: IPB065N15N3; TO-263-2; Rating 150 V 130 A; MPN/Spec Infineon IPB065N15N3 G
R18: 150k; R_0603_1608Metric; MPN/Spec 1 %, thick film
R19, R20, R21, R22, R27, R28, R29, R30: 10; R_0603_1608Metric; MPN/Spec 1 %
R23, R24, R25, R26, R31, R32, R33, R34: 10k; R_0603_1608Metric; MPN/Spec 1 %
U4: LTC7063; MSOP-12-1EP_3x4.039mm_P0.65mm_EP1.651x2.845mm; Rating 150 V; MPN/Spec LTC7063EMSE (MSOP-12)

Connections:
+12V: C47.1, D1.2 (A), U4.5 (Vcc), U4.6 (BGVcc); also elsewhere on the board
/Leg_A/BG_A: R27.1, R28.1, R29.1, R30.1, U4.8 (BG)
/Leg_A/BST_A: C46.1, D1.1 (K), U4.12 (BST)
/Leg_A/DT_A: R18.1, U4.4 (DT)
/Leg_A/TG_A: R19.1, R20.1, R21.1, R22.1, U4.11 (TG)
DRV_EN: U4.2 (EN); also elsewhere on the board
FAULT_N: U4.3 (~FLT); also elsewhere on the board
GND: C47.2, Q8.3 (S), Q9.3 (S), Q10.3 (S), Q11.3 (S), R18.2, R31.2, R32.2, R33.2, R34.2, U4.7 (BGRTN), U4.13 (SGND); also elsewhere on the board
unnamed: Q4.1 (G), R19.2, R23.1
unnamed: Q5.1 (G), R20.2, R24.1
unnamed: Q6.1 (G), R21.2, R25.1
unnamed: Q7.1 (G), R22.2, R26.1
unnamed: Q8.1 (G), R27.2, R31.1
unnamed: Q9.1 (G), R28.2, R32.1
unnamed: Q10.1 (G), R29.2, R33.1
unnamed: Q11.1 (G), R30.2, R34.1
PH_A: C46.2, Q4.3 (S), Q5.3 (S), Q6.3 (S), Q7.3 (S), Q8.2 (D), Q9.2 (D), Q10.2 (D), Q11.2 (D), R23.2, R24.2, R25.2, R26.2, U4.10 (SW); also elsewhere on the board
PWM_A: U4.1 (PWM); also elsewhere on the board
VBUS: Q4.2 (D), Q5.2 (D), Q6.2 (D), Q7.2 (D); also elsewhere on the board

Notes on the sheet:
4 LEG A (U4 LTC7063 + 2 x 4 IPB065N15N3)
Four FETs in parallel per switch, each with its own 10 Ω gate resistor (no gate-loop ringing between them) and 10 kΩ
pull-down (keeps them off while the driver is unpowered). Dead time from the DT resistor: 150 kΩ ≈ 140 ns.
Q4-Q11: IPB065N15N3 (150 V, 6.5 mΩ, D2PAK). High side: drains on VBUS, sources on PH. Low side: drains on PH, sources on GND.
Layout: the 2.2 µF ceramics across each leg's VBUS-GND, gate resistors at the gates, driver next to its leg.

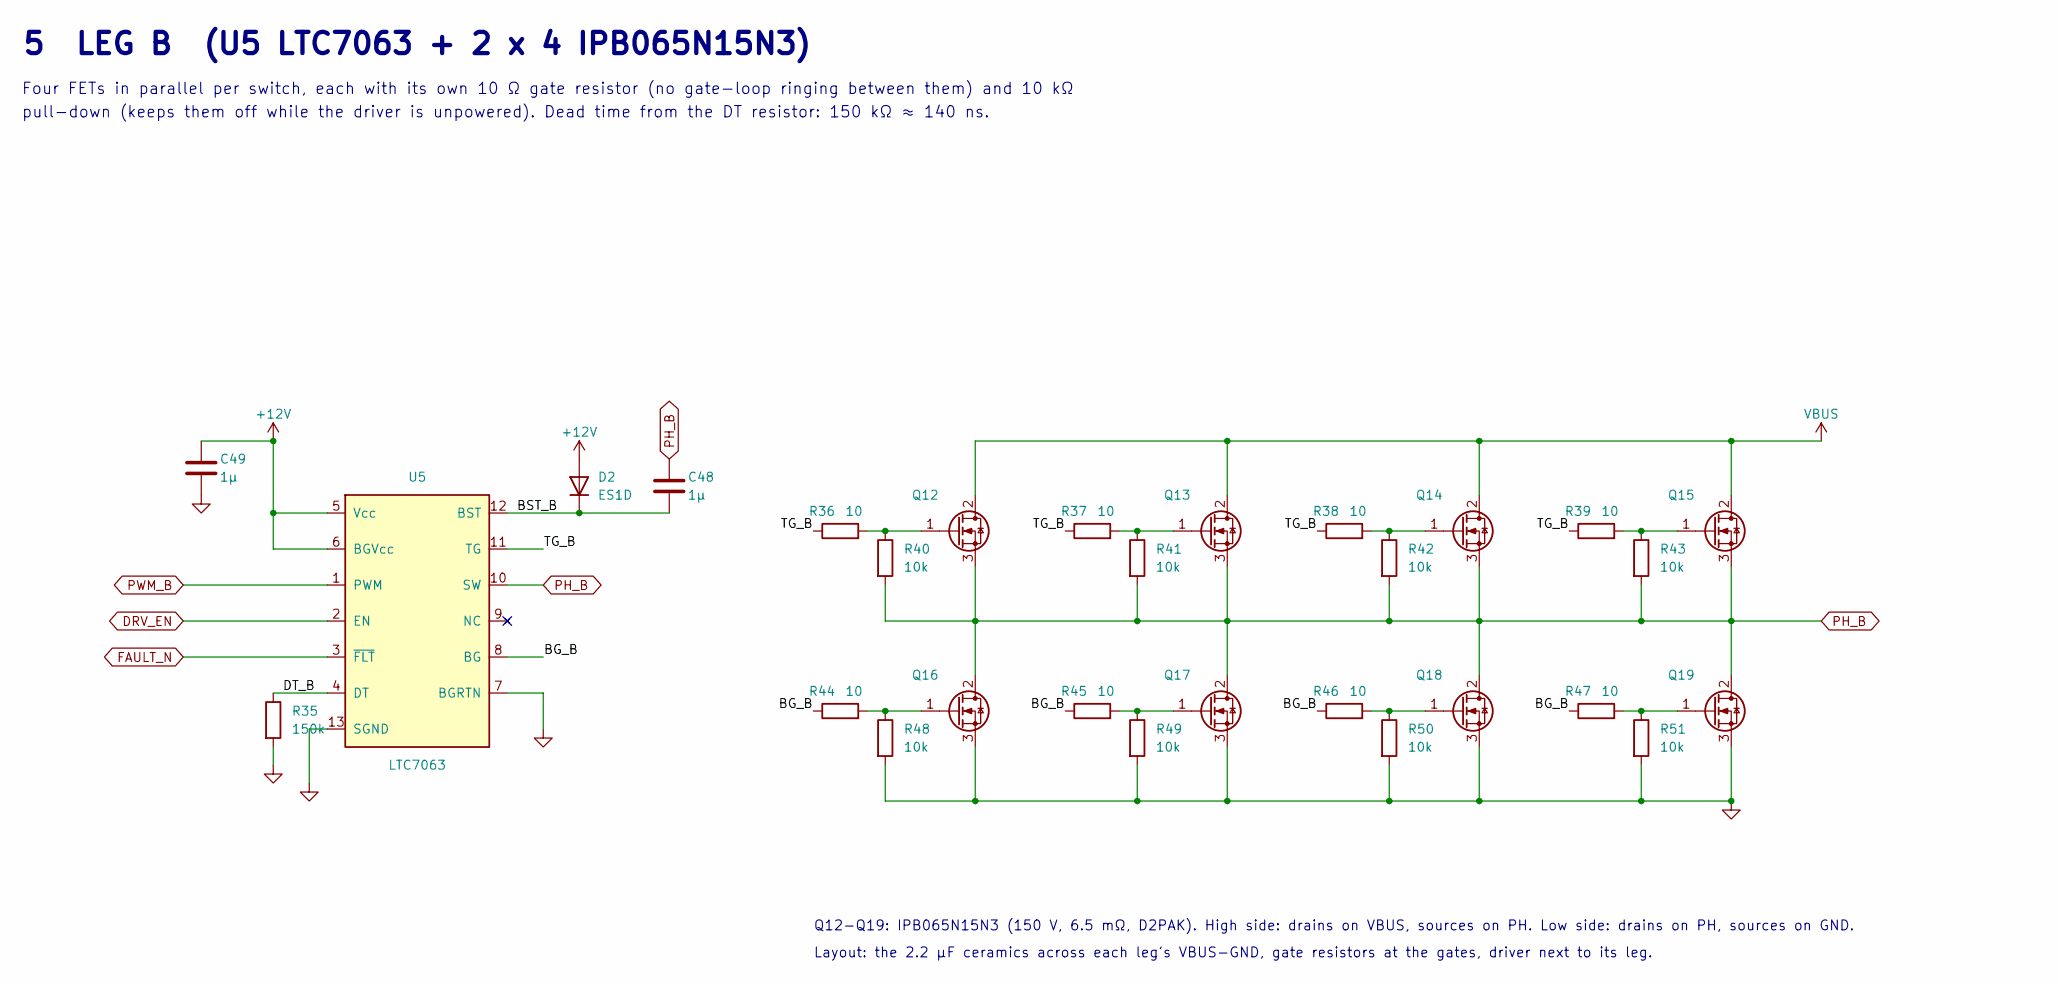
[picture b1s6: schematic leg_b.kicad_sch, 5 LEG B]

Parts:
C48, C49: 1µ; C_0805_2012Metric; Rating 25 V; MPN/Spec X7R
D2: ES1D; D_SMA; Rating 200 V 1 A; MPN/Spec ES1D
Q12, Q13, Q14, Q15, Q16, Q17, Q18, Q19: IPB065N15N3; TO-263-2; Rating 150 V 130 A; MPN/Spec Infineon IPB065N15N3 G
R35: 150k; R_0603_1608Metric; MPN/Spec 1 %, thick film
R36, R37, R38, R39, R44, R45, R46, R47: 10; R_0603_1608Metric; MPN/Spec 1 %
R40, R41, R42, R43, R48, R49, R50, R51: 10k; R_0603_1608Metric; MPN/Spec 1 %
U5: LTC7063; MSOP-12-1EP_3x4.039mm_P0.65mm_EP1.651x2.845mm; Rating 150 V; MPN/Spec LTC7063EMSE (MSOP-12)

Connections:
+12V: C49.1, D2.2 (A), U5.5 (Vcc), U5.6 (BGVcc); also elsewhere on the board
/Leg_B/BG_B: R44.1, R45.1, R46.1, R47.1, U5.8 (BG)
/Leg_B/BST_B: C48.1, D2.1 (K), U5.12 (BST)
/Leg_B/DT_B: R35.1, U5.4 (DT)
/Leg_B/TG_B: R36.1, R37.1, R38.1, R39.1, U5.11 (TG)
DRV_EN: U5.2 (EN); also elsewhere on the board
FAULT_N: U5.3 (~FLT); also elsewhere on the board
GND: C49.2, Q16.3 (S), Q17.3 (S), Q18.3 (S), Q19.3 (S), R35.2, R48.2, R49.2, R50.2, R51.2, U5.7 (BGRTN), U5.13 (SGND); also elsewhere on the board
unnamed: Q12.1 (G), R36.2, R40.1
unnamed: Q13.1 (G), R37.2, R41.1
unnamed: Q14.1 (G), R38.2, R42.1
unnamed: Q15.1 (G), R39.2, R43.1
unnamed: Q16.1 (G), R44.2, R48.1
unnamed: Q17.1 (G), R45.2, R49.1
unnamed: Q18.1 (G), R46.2, R50.1
unnamed: Q19.1 (G), R47.2, R51.1
PH_B: C48.2, Q12.3 (S), Q13.3 (S), Q14.3 (S), Q15.3 (S), Q16.2 (D), Q17.2 (D), Q18.2 (D), Q19.2 (D), R40.2, R41.2, R42.2, R43.2, U5.10 (SW); also elsewhere on the board
PWM_B: U5.1 (PWM); also elsewhere on the board
VBUS: Q12.2 (D), Q13.2 (D), Q14.2 (D), Q15.2 (D); also elsewhere on the board

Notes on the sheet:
5 LEG B (U5 LTC7063 + 2 x 4 IPB065N15N3)
Four FETs in parallel per switch, each with its own 10 Ω gate resistor (no gate-loop ringing between them) and 10 kΩ
pull-down (keeps them off while the driver is unpowered). Dead time from the DT resistor: 150 kΩ ≈ 140 ns.
Q12-Q19: IPB065N15N3 (150 V, 6.5 mΩ, D2PAK). High side: drains on VBUS, sources on PH. Low side: drains on PH, sources on GND.
Layout: the 2.2 µF ceramics across each leg's VBUS-GND, gate resistors at the gates, driver next to its leg.
